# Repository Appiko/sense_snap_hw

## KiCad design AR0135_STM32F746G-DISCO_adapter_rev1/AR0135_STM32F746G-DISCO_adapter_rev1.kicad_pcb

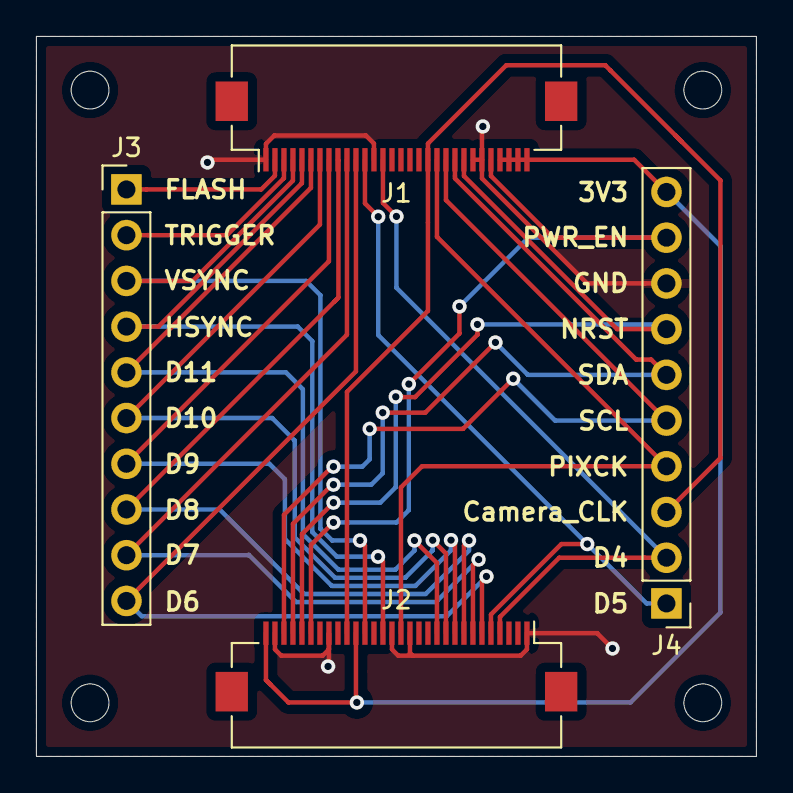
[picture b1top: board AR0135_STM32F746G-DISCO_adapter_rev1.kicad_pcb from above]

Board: 2 copper layers, 40.0 x 40.0 mm, 8 parts (0 on the bottom side), 20 nets.

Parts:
H1, H2, H3, H4: MountingHole; MountingHole_2.1mm
J1, J2: Conn_01x30; ArduCam_FPC_30pin_P0.50mm_Horizontal
J3, J4: Conn_01x10; PinHeader_1x10_P2.54mm_Vertical

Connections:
/3V3: J1.27, J1.28, J1.29, J1.30, J2.20, J2.30, J4.10
/Camera_CLK: J1.19, J2.21, J4.3
/D4: J1.14, J2.4, J4.2
/D5: J1.12, J2.5, J4.1
/D6: J1.11, J2.6, J3.10
/D7: J1.10, J2.7, J3.9
/D8: J1.9, J2.8, J3.8
/D9: J1.8, J2.9, J3.7
/D10: J1.7, J2.10, J3.6
/D11: J1.6, J2.11, J3.5
/DCMI_HSYNC: J1.5, J2.17, J3.4
/DCMI_NRST: J1.23, J2.26, J4.7
/DCMI_PIXCK: J1.20, J2.15, J4.4
/DCMI_PWR_EN: J1.26, J2.25, J4.9
/DCMI_SCL: J1.21, J2.28, J4.5
/DCMI_SDA: J1.22, J2.27, J4.6
/DCMI_VSYNC: J1.4, J2.19, J3.3
/FLASH: J1.2, J3.1
/GND: J1.1, J1.13, J1.24, J1.25, J2.1, J2.14, J2.16, J2.23, J2.29, J4.8
/TRIGGER: J1.3, J3.2

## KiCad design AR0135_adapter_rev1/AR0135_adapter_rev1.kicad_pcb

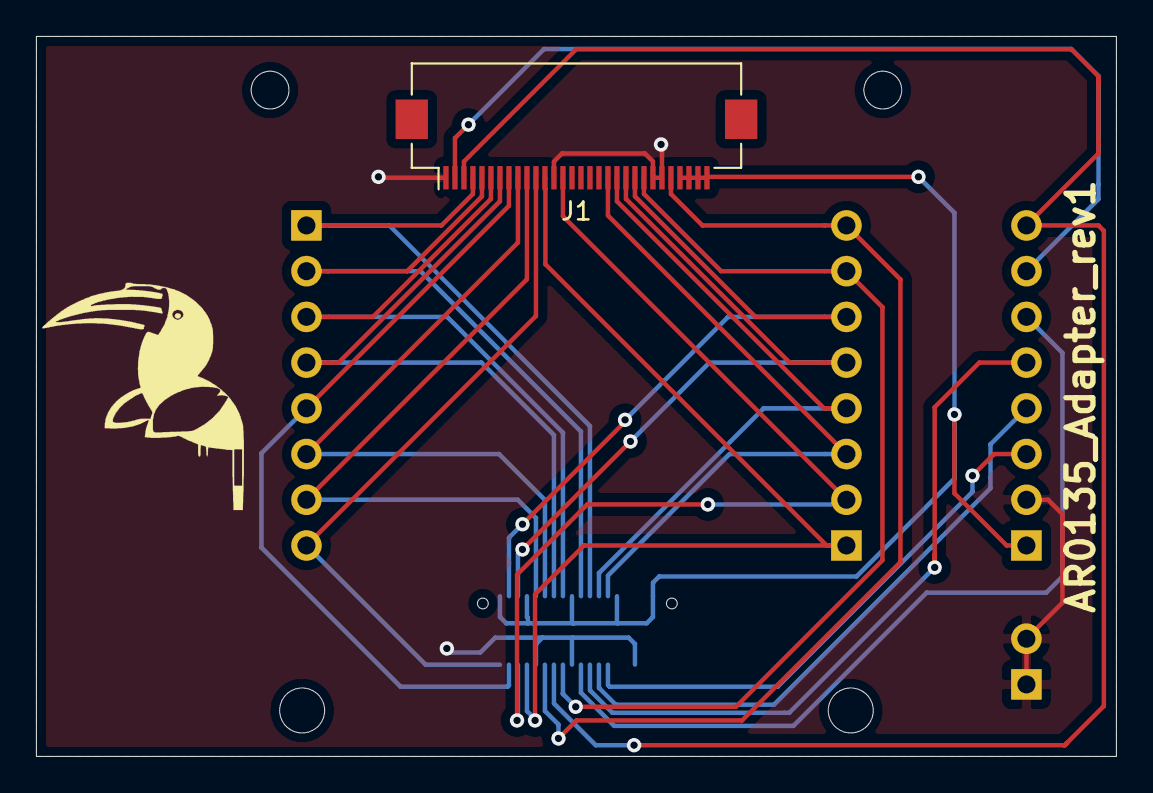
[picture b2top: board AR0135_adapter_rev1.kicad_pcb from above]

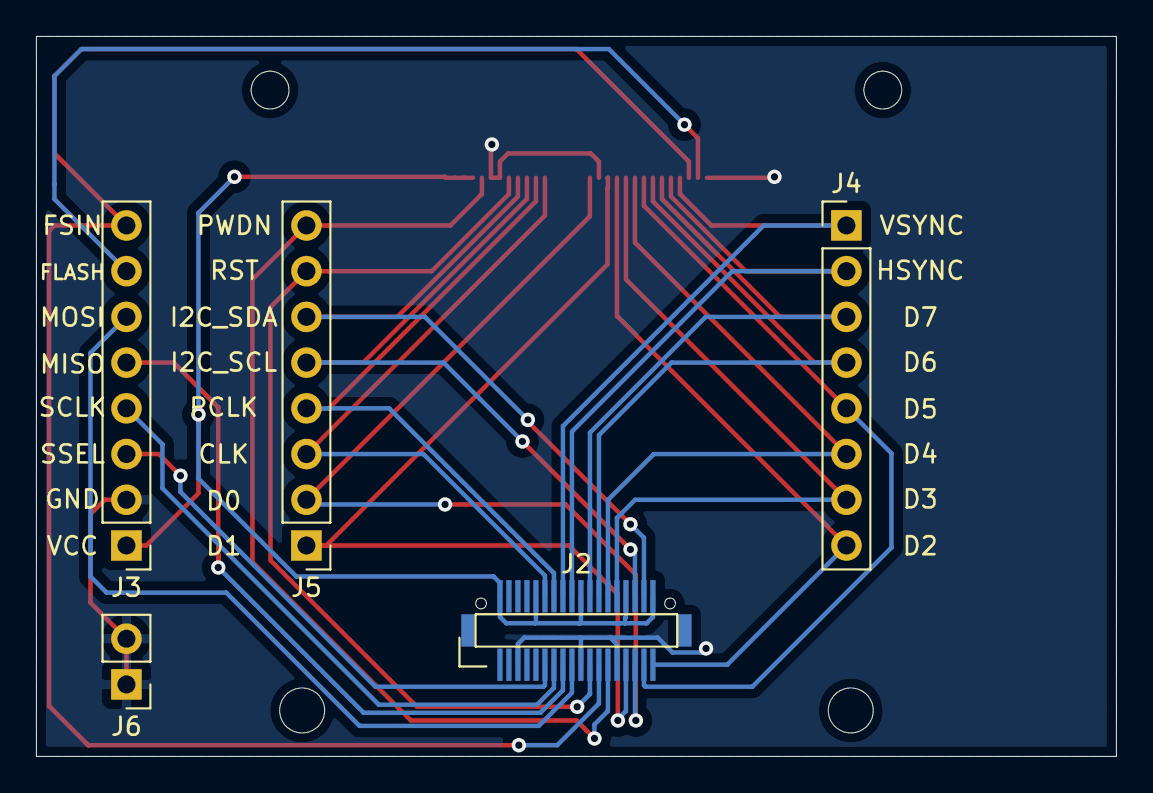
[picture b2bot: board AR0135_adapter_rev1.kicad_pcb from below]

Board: 2 copper layers, 60.0 x 40.0 mm, 10 parts (5 on the bottom side), 24 nets.

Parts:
J1: Conn_01x30; Hirose_FH12-30S-0.5SH_1x30-1MP_P0.50mm_Horizontal
J2: DF 12-36-DP; DF12(3.5)-36DP-0.5V(86)
J3, J4, J5: Conn_01x08; PinHeader_1x08_P2.54mm_Vertical
J6: Conn_01x02; PinHeader_1x02_P2.54mm_Vertical
MK1, MK2: Mounting_Hole; MountingHole_2.5mm
MK3, MK4: Mounting_Hole; MountingHole_2.1mm

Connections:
/DCMI_CLK: J1.19, J2.12, J5.3
/DCMI_D0: J1.14, J2.31, J5.2
/DCMI_D1: J1.12, J2.29, J5.1
/DCMI_D2: J1.11, J2.35, J4.8
/DCMI_D3: J1.10, J2.28, J4.7
/DCMI_D4: J1.9, J2.26, J4.6
/DCMI_D5: J1.8, J2.33, J4.5
/DCMI_D6: J1.7, J2.24, J4.4
/DCMI_D7: J1.6, J2.22, J4.3
/DCMI_FSIN: J1.3, J2.23, J3.8
/DCMI_HSYNC: J1.5, J2.18, J4.2
/DCMI_PCLK: J1.20, J2.14, J5.4
/DCMI_PWDN: J1.26, J2.25, J5.8
/DCMI_RST: J1.23, J2.21, J5.7
/DCMI_VSYNC: J1.4, J2.16, J4.1
/FLASH: J1.2, J3.7
/GND: J1.1, J1.13, J1.24, J1.25, J2.5, J2.19, J2.27, J3.2, J6.1, J6.2
/I2C1_SCL: J1.21, J2.32, J5.5
/I2C1_SDA: J1.22, J2.34, J5.6
/SPI3_MISO: J2.15, J3.5
/SPI3_MOSI: J2.17, J3.6
/SPI3_SCLK: J2.13, J3.4
/SPI3_SSEL: J2.11, J3.3
/VCC: J1.27, J1.28, J1.29, J1.30, J2.2, J2.10, J2.20, J2.30, J2.36, J3.1

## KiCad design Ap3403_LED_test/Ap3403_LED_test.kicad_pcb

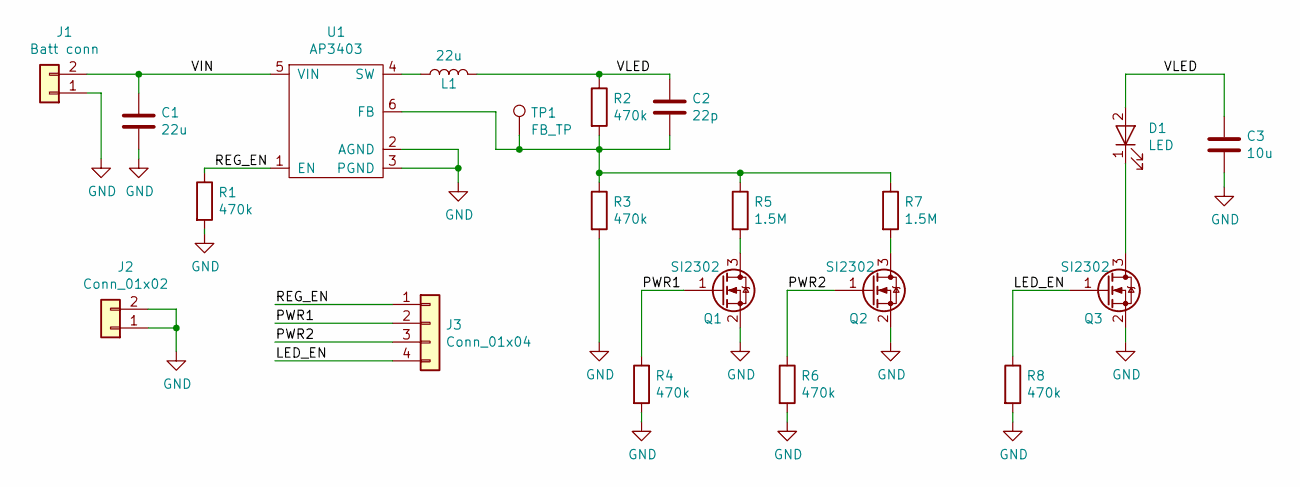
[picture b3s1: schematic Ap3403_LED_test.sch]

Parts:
C1: 22u; C_0805_HandSoldering
C2: 22p; C_0603_HandSoldering
C3: 10u; C_0805_HandSoldering
D1: LED; LED_D5.0mm
J1: Batt conn; Molex_KK-6410-02_02x2.54mm_Straight
J2: Conn_01x02; PinHeader_1x02_P2.54mm_Vertical
J3: Conn_01x04; PinHeader_1x04_P2.54mm_Vertical
L1: 22u; L_0805_2012Metric_Pad1.15x1.40mm_HandSolder
Q1, Q2, Q3: SI2302; SOT-23_Handsoldering
R1, R2, R3, R4, R6, R8: 470k; R_0603_HandSoldering
R5, R7: 1.5M; R_0603_HandSoldering
TP1: FB_TP; Measurement_Point_Round-SMD-Pad_Small
U1: AP3403; AP3403_U-DFN1616-6(Type G)

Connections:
/LED_EN: J3.4, Q3.1 (G), R8.1
/PWR1: J3.2, Q1.1 (G), R4.1
/PWR2: J3.3, Q2.1 (G), R6.1
/REG_EN: J3.1, R1.1, U1.1 (EN)
/VIN: C1.1, J1.2, U1.5 (VIN)
/VLED: C2.1, C3.1, D1.2 (A), L1.2, R2.1
GND: C1.2, C3.2, J1.1, J2.1, J2.2, Q1.2 (S), Q2.2 (S), Q3.2 (S), R1.2, R3.2, R4.2, R6.2, R8.2, U1.2 (AGND), U1.3 (PGND)
unnamed: C2.2, R2.2, R3.1, R5.1, R7.1, TP1.1, U1.6 (FB)
unnamed: D1.1 (K), Q3.3 (D)
unnamed: L1.1, U1.4 (SW)
unnamed: Q1.3 (D), R5.2
unnamed: Q2.3 (D), R7.2

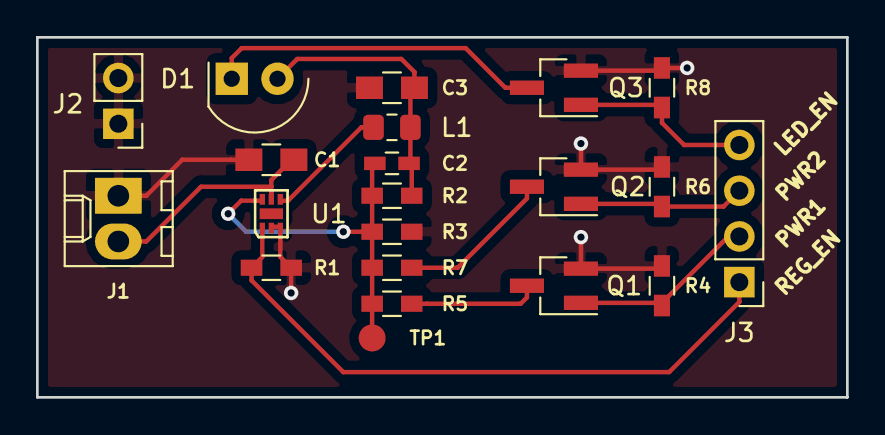
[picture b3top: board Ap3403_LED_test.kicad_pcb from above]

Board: 2 copper layers, 45.0 x 20.0 mm, 21 parts (0 on the bottom side), 12 nets.

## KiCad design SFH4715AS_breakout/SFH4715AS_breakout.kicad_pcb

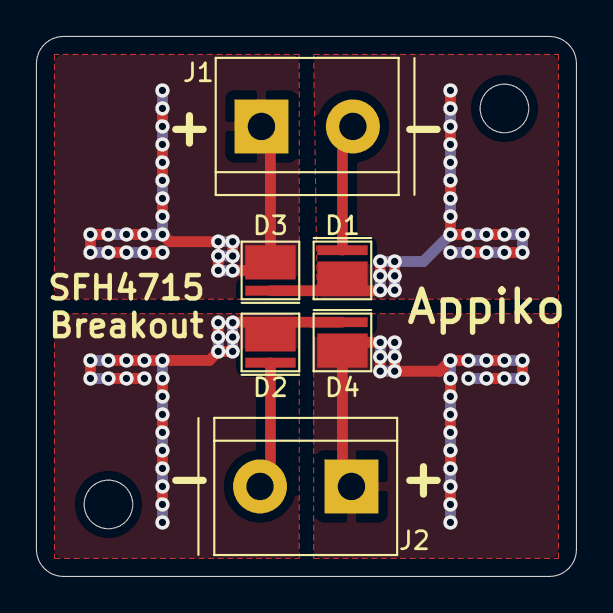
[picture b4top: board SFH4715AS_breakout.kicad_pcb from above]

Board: 2 copper layers, 30.0 x 30.0 mm, 8 parts (0 on the bottom side), 6 nets.

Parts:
D1, D2, D3, D4: SFH4715AS
J1, J2: Screw_Terminal_01x02; TerminalBlock_bornier-2_P5.08mm
MK1, MK2: Mounting_Hole; MountingHole_2.7mm_M2.5

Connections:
unnamed: D1.1, D3.2
unnamed: D1.2, J1.2
unnamed: D2.1, D4.2
unnamed: D2.2, J2.2
unnamed: D3.1, J1.1
unnamed: D4.1, J2.1

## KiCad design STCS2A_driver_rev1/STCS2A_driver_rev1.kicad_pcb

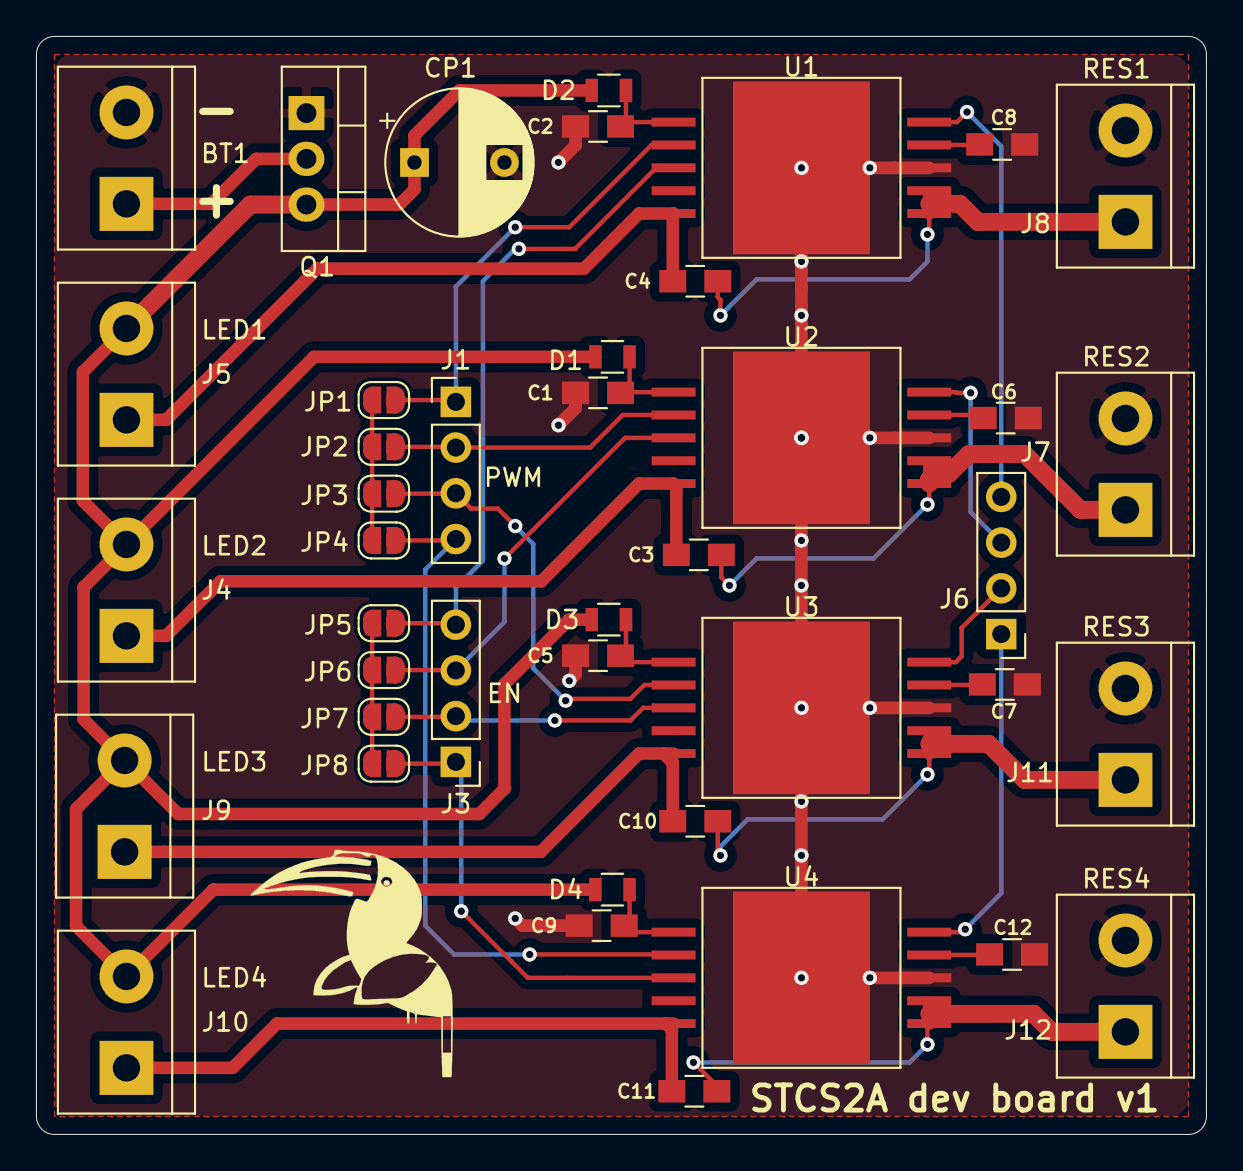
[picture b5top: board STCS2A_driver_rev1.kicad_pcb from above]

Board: 2 copper layers, 65.0 x 61.0 mm, 42 parts (0 on the bottom side), 33 nets.

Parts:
BT1: Battery; TerminalBlock_bornier-2_P5.08mm
C1, C2, C5, C9: 0.1uF; C_0805_HandSoldering
C3, C4, C10, C11: 0.47uF; C_0805_HandSoldering
C6, C7, C8, C12: 8pF; C_0805_HandSoldering
CP1: 100uF; CP_Radial_D8.0mm_P5.00mm
D1, D2, D3, D4: BAT46; R_0805
J1, J3, J6: Conn_01x04; PinHeader_1x04_P2.54mm_Vertical
J4, J5, J7, J8, J9, J10, J11, J12: Screw_Terminal_01x02; TerminalBlock_bornier-2_P5.08mm
JP1, JP2, JP3, JP4, JP5, JP6, JP7, JP8: SolderJumper_2_Open; SolderJumper-2_P1.3mm_Open_RoundedPad1.0x1.5mm
Q1: IRF9540; TO-220-3_Vertical
U1, U2, U3, U4: STCS2A; STCS2A_PowerSO-10

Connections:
/DISC1: J6.4, U1.10
/DISC2: J6.3, U2.10
/DISC3: J6.2, U3.10
/DISC4: J6.1, U4.10
/EN1: J3.4, JP5.1, U1.3
/EN2: J3.3, JP6.1, U2.3
/EN3: J3.2, JP7.1, U3.3
/EN4: J3.1, JP8.1, U4.3
/LED1: C4.1, J5.1, U1.5
/LED2: C3.1, J4.1, U2.5
/LED3: C10.1, J9.1, U3.5
/LED4: C11.1, J10.1, U4.5
/PWM1: J1.1, JP1.2, U1.2
/PWM2: J1.2, JP2.2, U2.2
/PWM3: J1.3, JP3.2, U3.2
/PWM4: J1.4, JP4.2, U4.2
/RES1: C4.2, J8.1, U1.6, U1.7
/RES2: C3.2, J7.1, U2.6, U2.7
/RES3: C10.2, J11.1, U3.6, U3.7
/RES4: C11.2, J12.1, U4.6, U4.7
GND: BT1.2, C1.1, C2.1, C5.1, C6.2, C7.2, C8.2, C9.1, C12.2, CP1.2, J7.2, J8.2, J11.2, J12.2, Q1.1, U1.8, U1.11, U2.8, U2.11, U3.8, U3.11, U4.8, U4.11
unnamed: BT1.1, Q1.2
unnamed: C1.2, D1.1, U2.1
unnamed: C2.2, D2.1, U1.1
unnamed: C5.2, D3.1, U3.1
unnamed: C6.1, U2.9
unnamed: C7.1, U3.9
unnamed: C8.1, U1.9
unnamed: C9.2, D4.1, U4.1
unnamed: C12.1, U4.9
unnamed: JP1.1, JP2.1, JP3.1, JP4.1
unnamed: JP5.2, JP6.2, JP7.2, JP8.2
VDD: CP1.1, D1.2, D2.2, D3.2, D4.2, J4.2, J5.2, J9.2, J10.2, Q1.3

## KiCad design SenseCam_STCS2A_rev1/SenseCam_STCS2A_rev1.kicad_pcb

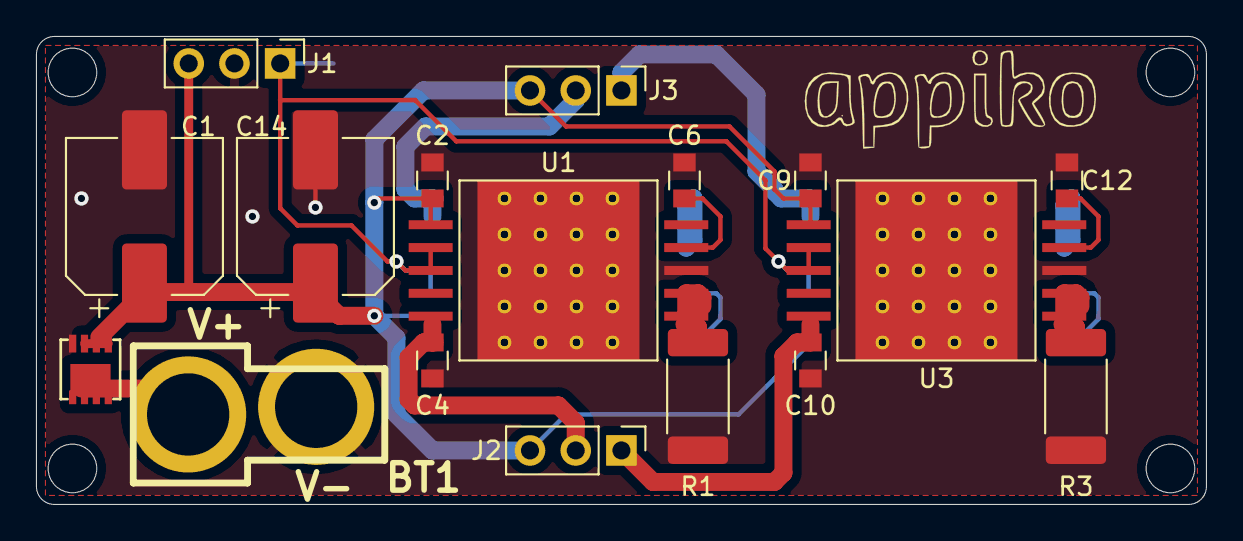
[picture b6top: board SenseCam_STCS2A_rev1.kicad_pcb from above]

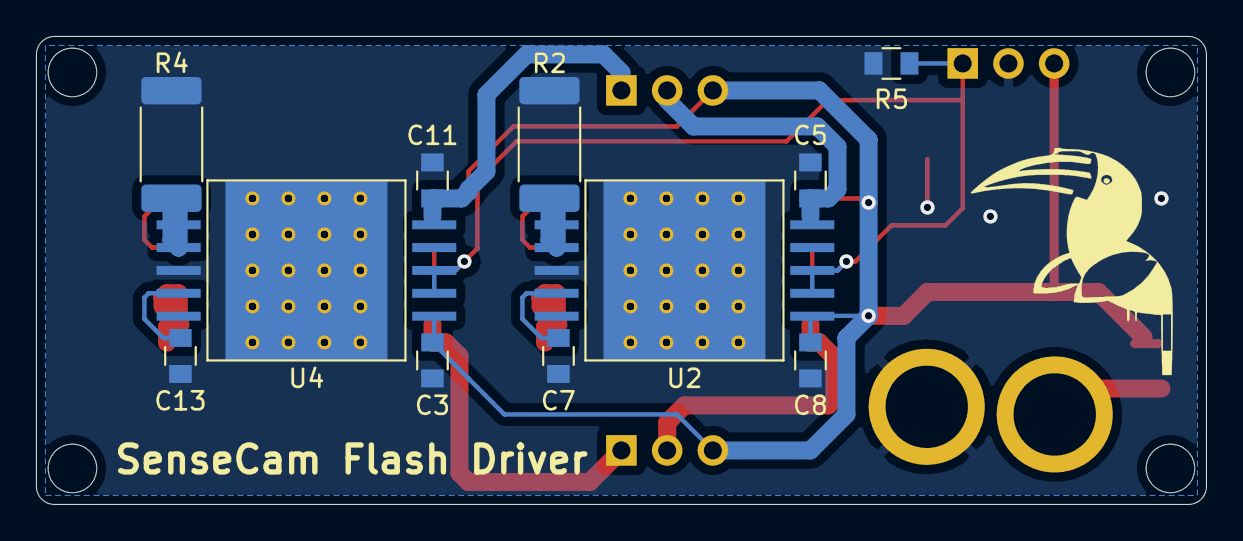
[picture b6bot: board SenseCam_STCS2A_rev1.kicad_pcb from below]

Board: 2 copper layers, 65.0 x 26.0 mm, 32 parts (11 on the bottom side), 16 nets.

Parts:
BT1: LiPo 2s; DEANS
C1, C14: 100uF; CP_Elec_8x10.5
C2, C3, C8, C9: 100nF; C_0805
C4, C5, C10, C11: 0.47uF; C_0805
C6, C7, C12, C13: 0.1nF; C_0805
J1, J2, J3: Conn_01x03; PinHeader_1x03_P2.54mm_Vertical
MK1, MK2, MK3, MK4: Mounting_Hole; MountingHole_2.7mm_M2.5
Q1: SiSH615ADN; PowerPAK-1212-8
R1, R2, R3, R4: 0R033; R_2512_6332Metric_Pad1.52x3.35mm_HandSolder
R5: 10k; C_0805
U1, U2, U3, U4: STCS2A; STCS2A_PowerSO-10

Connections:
/LED1: C4.2, J2.2, U1.5
/LED2: C10.1, J2.1, U3.5
/LED3: C5.2, J3.2, U2.5
/LED4: C11.2, J3.1, U4.5
/LED_EN: J1.1, R5.1, U1.2, U1.3, U2.2, U2.3, U3.2, U3.3, U4.2, U4.3
/VIN: C1.1, C2.1, C3.1, C8.1, C9.1, C14.1, J1.3, J2.3, J3.3, Q1.3, U1.1, U2.1, U3.1, U4.1
GND: BT1.2, C1.2, C2.2, C3.2, C4.1, C5.1, C6.1, C7.1, C8.2, C9.2, C10.2, C11.1, C12.1, C13.1, C14.2, J1.2, Q1.1, R1.2, R2.2, R3.2, R4.2, R5.2, U1.8, U1.11, U2.8, U2.11, U3.8, U3.11, U4.8, U4.11
unnamed: BT1.1, Q1.2
unnamed: C6.2, U1.9
unnamed: C7.2, U2.9
unnamed: C12.2, U3.9
unnamed: C13.2, U4.9
unnamed: R1.1, U1.6, U1.7
unnamed: R2.1, U2.6, U2.7
unnamed: R3.1, U3.6, U3.7
unnamed: R4.1, U4.6, U4.7

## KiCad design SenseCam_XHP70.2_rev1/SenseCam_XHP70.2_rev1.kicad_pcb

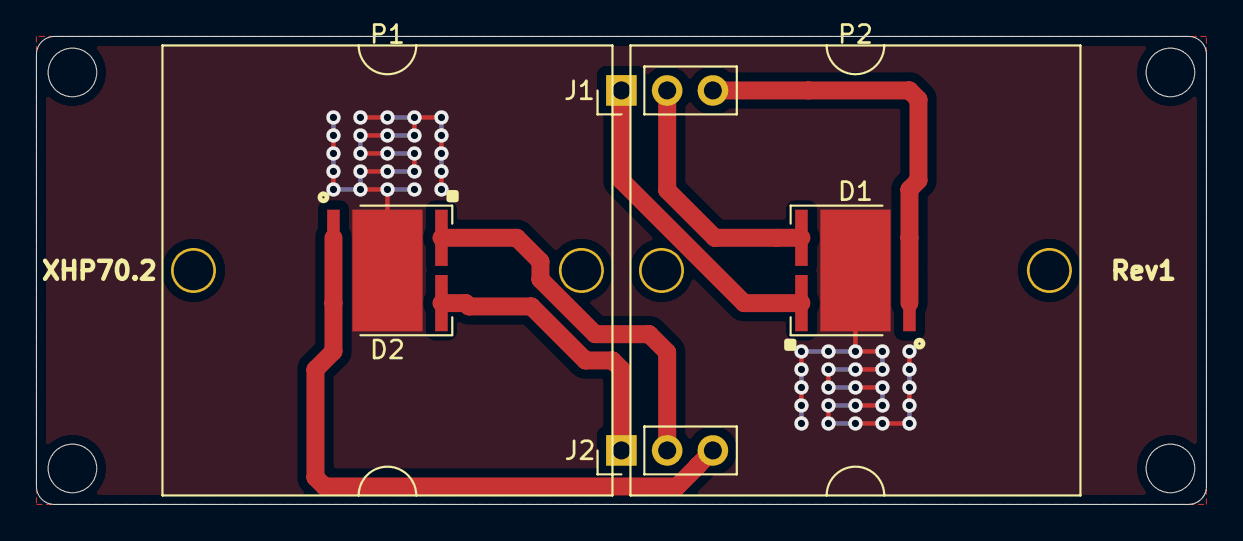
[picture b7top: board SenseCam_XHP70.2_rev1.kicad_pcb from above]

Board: 2 copper layers, 65.0 x 26.0 mm, 10 parts (0 on the bottom side), 6 nets.

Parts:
D1, D2: XHP70.2; LED_Cree-XHP70
J1, J2: Conn_01x03; PinHeader_1x03_P2.54mm_Vertical
MK1, MK2, MK3, MK4: Mounting_Hole; MountingHole_2.7mm_M2.5
P1, P2: CA16372_HB-SQ-WWW

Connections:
/LED1: D1.1, J1.2
/LED2: D1.2, J1.1
/LED3: D2.1, J2.1
/LED4: D2.2, J2.2
/THERMAL: D1.5, D2.5
/VIN: D1.3, D1.4, D2.3, D2.4, J1.3, J2.3

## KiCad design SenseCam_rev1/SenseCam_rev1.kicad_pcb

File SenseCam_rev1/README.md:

# SenseCam revision 1

This repo contains the Kicad PCB design of the first revision of SenseCam base board containing the STM32H750. This board is designed to interface an image sensor, interface two SD cards with both the SDMMC and multiple low power buck regulators to power the microcontroller.

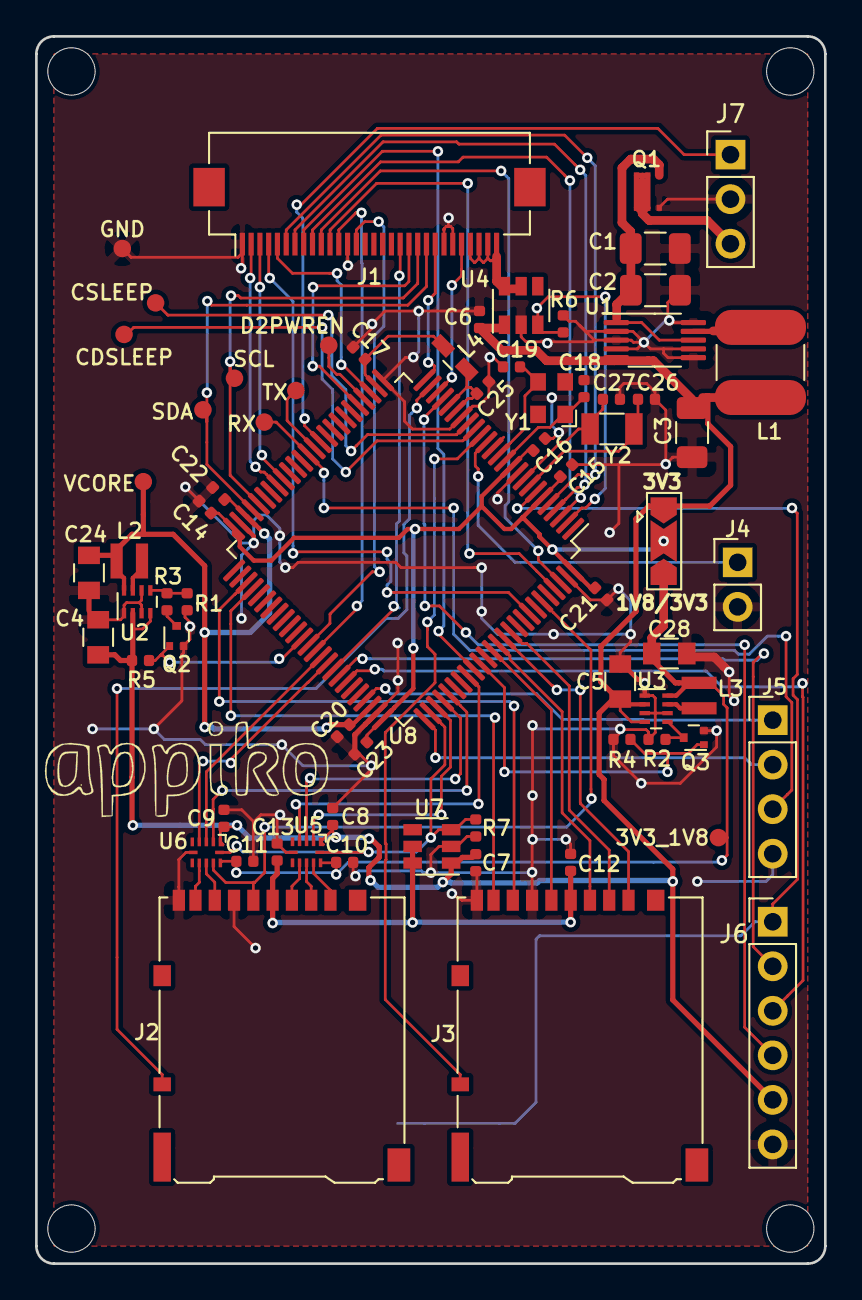
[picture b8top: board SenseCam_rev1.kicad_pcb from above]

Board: 2 copper layers, 45.0 x 70.0 mm, 75 parts (1 on the bottom side), 75 nets.

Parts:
3V3_1V8: VDD_1V8_3V3; testpoint_micro
C1, C2, C3: 22uF; C_1206_3216Metric
C4, C5, C24, C28: 4.7uF; C_0805
C6, C7, C8, C9, C10, C11, C12, C13, C14, C15, C16, C17, C20, C21, C22, C23, C25: 0.1uF; C_0402_1005Metric
C18, C19: 8pF; C_0402_1005Metric
C26, C27: 12pF; C_0402_1005Metric
CDSLEEP: CDSLEEP; testpoint_micro
CSLEEP: CSLEEP; testpoint_micro
D2PWREN: D2PWREN; testpoint_micro
GND: GND; testpoint_micro
J1: Conn_01x30; ArduCam_FPC_30pin_P0.50mm_Horizontal
J2, J3: Micro_SD_Card_Det_Hirose_DM3AT; microSD_HC_Hirose_DM3AT-SF-PEJM5
J4: Conn_01x02; PinHeader_1x02_P2.54mm_Vertical
J5: Conn_01x04; PinHeader_1x04_P2.54mm_Vertical
J6: Conn_01x06; PinHeader_1x06_P2.54mm_Vertical
J7: Flash board; PinHeader_1x03_P2.54mm_Vertical
JP1: SolderJumper_3_Open; SolderJumper-3_P2.0mm_Open_TrianglePad1.0x1.5mm
L1: 10uH; L_5mm_SMD
L2, L3: 2.2uH; L_2.4mm_SMD
L4: MPZ1608S331ATA00; C_0603_HandSoldering
MK1, MK2, MK3, MK4: Mounting_Hole; MountingHole_2.7mm_M2.5
Q1: SQA403EJ; SQA403EJ-SC70-6
Q2, Q3: NTK3043NT1G; SOT-723
R1: 51k; C_0402_1005Metric
R2, R6, R7: 270k; C_0402_1005Metric
R3: 22k; C_0402_1005Metric
R4, R5: 1M; C_0402_1005Metric
RX: UART_TX; testpoint_micro
SCL: I2C_SCL; testpoint_micro
SDA: I2C_SDA; testpoint_micro
SW1: SW_SPST; SW_Push_1P1T_NO_CK_KSC7xxJ
TX: UART_RX; testpoint_micro
U1: TPS62056DGS; VSSOP-10_3x3mm_P0.5mm
U2: TPS62841; WSON-8-TPS62840
U3: TPS62840; WSON-8-TPS62840
U4, U7: TPS22917; SOT-23-6
U5, U6: TXB0304RUT; TXB0304_12UQFN
U8: STM32H750VB; LQFP-100_14x14mm_P0.5mm
VCORE: VDD_CORE; testpoint_micro
Y1: 20MHz; Crystal_SMD_4Pin_2.5x2.0mm
Y2: 32768; Crystal_SMD_3215-2Pin_3.2x1.5mm

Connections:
+3V3: C3.1, C4.1, C5.1, C6.1, C7.1, C8.2, C9.2, J6.5, JP1.1, L1.2, R5.1, U1.5, U2.2, U2.4, U3.2, U3.4, U4.1, U5.1, U6.1, U7.1
/1V4CORE_EN*: Q2.1, R5.2, U8.62
/1V8IO_EN: Q3.1, R4.1, U8.85
/ArduCam SDcard/SD_CMD: J2.3, U5.8
/ArduCam SDcard/SD_DAT0: J2.7, U6.9
/ArduCam SDcard/SD_DAT1: J2.8, U6.8
/ArduCam SDcard/SD_DAT2: J2.1, U5.10
/ArduCam SDcard/SD_DAT3: J2.2, U5.9
/ArduCam SDcard/VCC_ARDU: J1.27, J1.28, J1.29, J1.30, U4.5, U4.6
/ArduCam SDcard/VCC_SD: C12.1, C13.1, J2.4, J3.4, U7.5, U7.6
/CAM_FLASH: J1.2, U8.43
/CAM_FLASH_PULSE: J7.1, U8.36
/CAM_PWR_EN: R6.1, U4.3, U8.2
/CAM_STANDBY: J1.26, U8.23
/CAM_TRIGGER: J1.3, U8.42
/DCMI_CAMCLK: J1.19, U8.67
/DCMI_D0: J1.14, U8.63
/DCMI_D1: J1.12, U8.64
/DCMI_D2: J1.11, U8.97
/DCMI_D3: J1.10, U8.98
/DCMI_D4: J1.9, U8.3
/DCMI_D5: J1.8, U8.84
/DCMI_D6: J1.7, U8.4
/DCMI_D7: J1.6, U8.5
/DCMI_HSYNC: J1.5, U8.28
/DCMI_NRST: J1.23, U8.25
/DCMI_PIXCLK: J1.20, U8.30
/DCMI_SCL: J1.21, SCL.1, U8.46
/DCMI_SDA: J1.22, SDA.1, U8.47
/DCMI_VSYNC: J1.4, U8.93
/H7 pins/CDSLEEP: CDSLEEP.1, U8.17
/H7 pins/CSLEEP: CSLEEP.1, U8.18
/H7 pins/D2PWREN: D2PWREN.1, U8.29
/H7 pins/LDR_IN: J4.1, U8.15
/H7 pins/LPUART_RX: J6.3, U8.69
/H7 pins/LPUART_TX: J6.2, U8.68
/H7 pins/SENSEBE_WKUP: J6.4, U8.22
/H7 pins/STM_NRF_BUTTON: J6.1, SW1.1, U8.7
/H7 pins/SWDCLK: J5.2, U8.76
/H7 pins/SWDIO: J5.1, U8.72
/H7 pins/UART7_RX: TX.1, U8.37
/H7 pins/UART7_TX: J5.3, RX.1, U8.38
/H7 pins/VBAT: C14.1, C15.1, C16.1, C17.1, C21.1, C23.1, JP1.2, L4.1, U8.6, U8.11, U8.27, U8.50, U8.75, U8.100
/H7 pins/VDDA: C25.1, L4.2, U8.20, U8.21
/Power/BAT_IN: J7.3, Q1.2
/Power/VBAT_2S: C1.1, C2.1, Q1.3, U1.1, U1.8
/SD1_CLK: U6.2, U8.80
/SD1_CLKIN: J2.5, U6.10, U8.95
/SD1_CMD: U5.4, U8.83
/SD1_DAT0: U6.3, U8.65
/SD1_DAT1: U6.4, U8.66
/SD1_DAT2: U5.2, U8.78
/SD1_DAT3: U5.3, U8.79
/SD1_DECT: J2.10, U8.24
/SD2_CLK: J3.5, U8.87
/SD2_CMD: J3.3, U8.88
/SD2_DAT0: J3.7, U8.53
/SD2_DAT1: J3.8, U8.54
/SD2_DAT2: J3.1, U8.89
/SD2_DAT3: J3.2, U8.90
/SD2_DECT: J3.10, U8.16
/SD_PWR_EN: R7.1, U5.12, U6.12, U7.3, U8.77
/VDD_1V8_3V3: 3V3_1V8.1, C10.2, C11.2, C28.1, JP1.3, L3.2, U3.8, U5.11, U6.11
/VDD_CORE: C20.1, C22.1, C24.1, L2.2, U2.8, U8.48, U8.73, VCORE.1
GND: C1.2, C2.2, C3.2, C4.2, C5.2, C6.2, C7.2, C8.1, C9.1, C10.1, C11.1, C12.2, C13.2, C14.2, C15.2, C16.2, C17.2, C18.2, C19.2, C20.2, C21.2, C22.2, C23.2, C24.2, C25.2, C26.2, C27.2, C28.2, GND.1, J1.1, J1.13, J1.24, J1.25, J2.6, J2.9, J3.6, J3.9, J4.2, J5.4, J6.6, J7.2, Q1.1, Q2.2, Q3.2, R1.2, R2.2, R4.2, R6.2, R7.2, SW1.2, U1.2, U1.3, U1.4, U1.6, U1.7, U1.10, U2.1, U2.3, U2.6, U3.1, U3.3, U3.6, U4.2, U5.6, U6.6, U7.2, U8.10, U8.19, U8.26, U8.49, U8.74, U8.99
unnamed: C18.1, U8.12, Y1.1
unnamed: C19.1, U8.13, Y1.2
unnamed: C26.1, U8.8, Y2.1
unnamed: C27.1, U8.9, Y2.2
unnamed: L1.1, U1.9
unnamed: L2.1, U2.7
unnamed: L3.1, U3.7
unnamed: Q2.3, R3.2
unnamed: Q3.3, R2.1, U3.5
unnamed: R1.1, R3.1, U2.5
